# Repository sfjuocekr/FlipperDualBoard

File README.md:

# FlipperDualBoard
A Flipper Zero development board implementing the SPI handles from CFW!

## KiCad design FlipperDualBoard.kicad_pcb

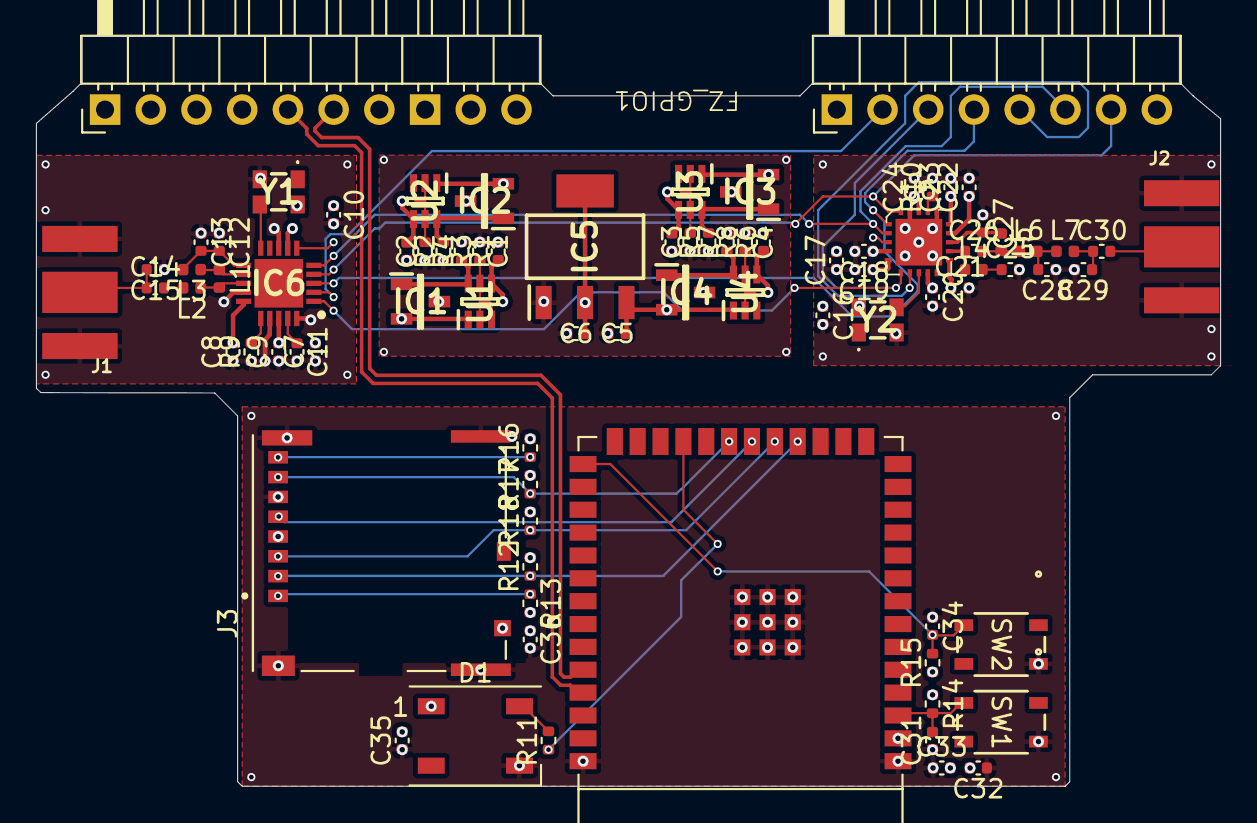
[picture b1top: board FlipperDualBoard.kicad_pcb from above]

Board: 4 copper layers, 65.8 x 41.7 mm, 82 parts (0 on the bottom side), 50 nets.

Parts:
C1, C2, C3, C4, C10, C16, C18, C19, C33, C35, C36: 100nF X7R; C_0402_1005Metric
C5: 10µF NPO; C_0402_1005Metric
C6, C32: 22µF NPO; C_0402_1005Metric
C7, C17: 4.7µF NPO; C_0402_1005Metric
C8, C20, C22: 10nF X7R; C_0402_1005Metric
C9: 1nF X7R; C_0402_1005Metric
C11: 33nF X7R; C_0402_1005Metric
C12: 2.2nF X7R; C_0402_1005Metric
C13: 4.7pF NPO; C_0402_1005Metric
C14: 1.5pF NPO; C_0402_1005Metric
C15: 1pF NPO; C_0402_1005Metric
C21, C23, C24, C25, C30: 220pF NPO; C_0402_1005Metric
C26, C27: 3.9pF NPO; C_0402_1005Metric
C28: 8.2pF NPO; C_0402_1005Metric
C29: 5.6pF NPO; C_0402_1005Metric
C31, C34: 1µF NPO; C_0402_1005Metric
D1: WS2812B; LED_WS2812B_PLCC4_5.0x5.0mm_P3.2mm
FZ_GPIO1: FZ_GPIO
IC1, IC2, IC3, IC4: DMP1045U-7; SOT96P240X120-3N
IC5: AZ1117CH2-3.3TRG1; SOT230P700X180-4N
IC6: nRF24L01P; QFN50P400X400X95-21N-D
J1, J2: Conn_SMA_RF2-143-T-17-50-G; RF_SMA_BoardEdge_RF2-143-T-17-50-G
J3: 503398-1892; MOLEX_503398-1892
L1: 8.2nH; L_0402_1005Metric
L2: 3.9nH; L_0402_1005Metric
L3, L4, L5, L7: 27nH; L_0402_1005Metric
L6: 22nH; L_0402_1005Metric
R1, R2, R3, R4, R5, R6, R7, R8: 100k; R_0402_1005Metric
R9: 22k; R_0402_1005Metric
R10: 56k; R_0402_1005Metric
R11: 220; R_0402_1005Metric
R12, R13, R14, R15, R16, R17, R18: 10k; R_0402_1005Metric
SW1, SW2: SKRPABE010; SW4_SKRPABE010_ALPS
U1, U2, U3, U4: MMDT2907A-7-F; SOT65P210X110-6N
U5: ESP32-S3-WROOM-1
U6: CC1101RGPR; QFN-20-1EP_4x4mm_RevA
Y1: TG2520SMN_16.0000M-MCGNNM3; TG2520SMN160000MMCGNNM3
Y2: TG2520SMN_26.0000M-MCGNNM3; TG2520SMN160000MMCGNNM3

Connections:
/ESP32/BOOT: C34.2, R15.2, SW2.2, U5.27 (GPIO0/BOOT)
/ESP32/CLK: J3.5 (CLK), U5.20 (GPIO12/TOUCH12/ADC2_CH1/FSPICLK/FSPIIO6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)
/ESP32/CMD: J3.3 (CMD), R18.1, U5.19 (GPIO11/TOUCH11/ADC2_CH0/FSPID/FSPIIO5/S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)
/ESP32/DATA0: J3.7 (DAT0), R17.1, U5.21 (GPIO13/TOUCH13/ADC2_CH2/FSPIQ/FSPIIO7/S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)
/ESP32/DATA1: J3.8 (DAT1), R16.1
/ESP32/DATA2: J3.1 (DAT2), R13.1
/ESP32/DATA3: J3.2 (CD/DAT3^2), R12.1, U5.18 (GPIO10/TOUCH10/ADC1_CH9/FSPICS0/FSPIIO4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)
/ESP32/EN: C31.2, R14.2, SW1.2, U5.3 (EN)
/ESP32/U+: FZ_GPIO1.14 (PB7), U5.37 (U0TXD/GPIO43/CLK_OUT1)
/ESP32/U-: FZ_GPIO1.13 (PB6), U5.36 (U0RXD/GPIO44/CLK_OUT2)
/Power Supply/+3v3 IN: C2.1, FZ_GPIO1.9 (3.3v), IC2.3 (D), U2.4 (E2)
/Power Supply/+3v3 LDO: C1.1, C6.1, IC1.3 (D), IC5.2 (ADJ/GND_1), IC5.4 (ADJ/GND_2), U1.4 (E2)
/Power Supply/+3v3 OUT: C7.2, C8.2, C9.2, C10.1, C16.1, C17.2, C18.1, C19.1, C20.1, C21.1, C22.1, C23.1, C24.1, C32.2, C33.2, C35.2, C36.1, D1.1 (VDD), IC1.2 (S), IC2.2 (S), IC6.7 (VDD_1), IC6.15 (VDD_2), IC6.18 (VDD_3), J3.4 (VDD), R12.2, R13.2, R14.1, R15.1, R16.2, R17.2, R18.2, U1.1 (E1), U2.1 (E1), U5.2 (3V3), U6.4 (DVDD), U6.5 (DCOUPL), U6.9 (AVDD), U6.11 (AVDD), U6.14 (AVDD), U6.15 (AVDD), U6.18 (DGUARD), Y1.4 (VCC), Y2.4 (VCC)
/Power Supply/+5v IN: C3.1, FZ_GPIO1.1 (5v), IC3.3 (D), U3.4 (E2)
/Power Supply/+5v OUT: C5.1, IC3.2 (S), IC4.2 (S), IC5.3 (OUTPUT), U3.1 (E1), U4.1 (E1)
/Power Supply/+5v USB: C4.1, IC4.3 (D), U4.4 (E2)
/Power Supply/S0: IC2.1 (G), R4.1, U2.6 (C1)
/Power Supply/S1: IC3.1 (G), R7.1, U3.6 (C1)
/Power Supply/S2: IC1.1 (G), R3.1, U1.6 (C1)
/Power Supply/S3: IC4.1 (G), R8.1, U4.6 (C1)
/SPI Modules/CC1101/RF_N: C27.2, L5.1, U6.13 (RF_N)
/SPI Modules/CC1101/RF_P: C26.1, L4.1, U6.12 (RF_P)
/SPI Modules/CE: FZ_GPIO1.6 (PB2), IC6.1 (CE), U6.6 (GDO0)
/SPI Modules/CS0: FZ_GPIO1.4 (PA4), U6.7 (CSn)
/SPI Modules/CS1: FZ_GPIO1.7 (PC3), IC6.2 (CSN)
/SPI Modules/MISO: FZ_GPIO1.3 (PA6), IC6.5 (MISO), U6.2 (SO(GDO1))
/SPI Modules/MOSI: FZ_GPIO1.2 (PA7), IC6.4 (MOSI), U6.20 (SI)
/SPI Modules/SCK: FZ_GPIO1.5 (PB3), IC6.3 (SCK), U6.1 (SCLK)
GND: C1.2, C2.2, C3.2, C4.2, C5.2, C6.2, C7.1, C8.1, C9.1, C10.2, C11.2, C12.1, C13.1, C15.1, C16.2, C17.1, C18.2, C19.2, C20.2, C21.2, C22.2, C23.2, C24.2, C25.2, C27.1, C28.1, C29.2, C31.1, C32.1, C33.1, C34.1, C35.1, C36.2, D1.3 (VSS), FZ_GPIO1.8 (GND), FZ_GPIO1.11 (GND), FZ_GPIO1.18 (GND), IC5.1 (INPUT), IC6.8 (VSS_1), IC6.14 (VSS_2), IC6.17 (VSS_3), IC6.20 (VSS_4), J1.2, J2.2, J3.6 (VSS), J3.9 (VSS__1), J3.P1 (SHIELD), J3.P2 (SHIELD__1), J3.P3 (SHIELD__2), J3.P4 (SHIELD__3), R1.2, R2.2, R3.2, R4.2, R5.2, R6.2, R7.2, R8.2, R9.1, R10.2, SW1.3, SW2.3, U5.1 (GND), U5.40 (GND), U5.41 (GND), U6.16 (GND), U6.19 (GND), U6.21 (EP_GND), Y1.2 (GND), Y2.2 (GND)
unnamed: C14.1, C15.2, J1.1
unnamed: C14.2, L2.2
unnamed: C25.1, L4.2
unnamed: C26.2, L5.2, L6.1
unnamed: C28.2, L6.2, L7.1
unnamed: C29.1, C30.1, L7.2
unnamed: C30.2, J2.1
unnamed: D1.4 (DIN), R11.2
unnamed: IC6.12 (ANT1), L1.1, L3.1
unnamed: IC6.13 (ANT2), L1.2, L2.1
unnamed: C11.1, IC6.19 (DVDD)
unnamed: IC6.16 (IREF), R9.2
unnamed: C12.2, C13.2, IC6.11 (VDD_PA), L3.2
unnamed: IC6.10 (XC1), Y1.3 (OUT)
unnamed: R1.1, U1.2 (B1), U1.3 (C2), U1.5 (B2)
unnamed: R2.1, U2.2 (B1), U2.3 (C2), U2.5 (B2)
unnamed: R5.1, U3.2 (B1), U3.3 (C2), U3.5 (B2)
unnamed: R6.1, U4.2 (B1), U4.3 (C2), U4.5 (B2)
unnamed: R11.1, U5.23 (GPIO21)
unnamed: R10.1, U6.17 (RBIAS)
unnamed: U6.8 (XOSC_Q1), Y2.3 (OUT)

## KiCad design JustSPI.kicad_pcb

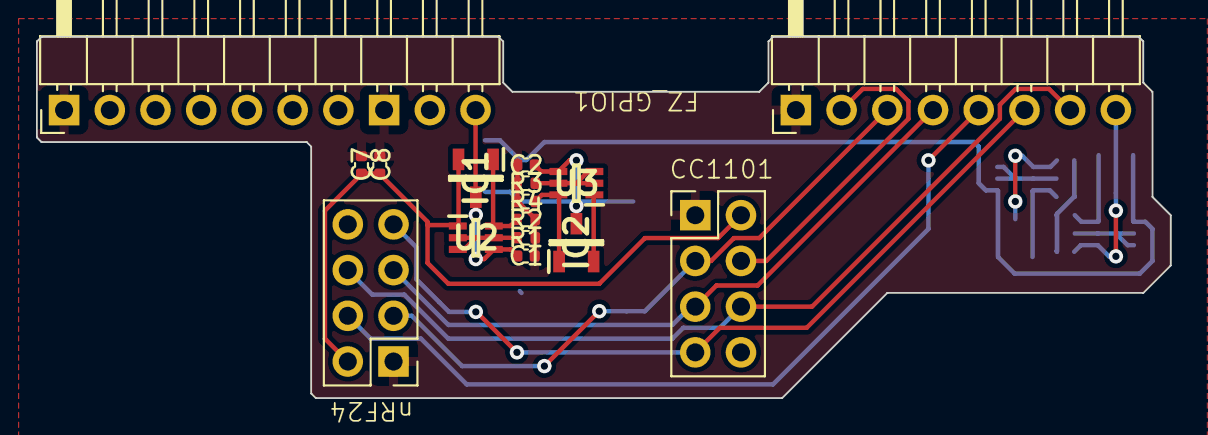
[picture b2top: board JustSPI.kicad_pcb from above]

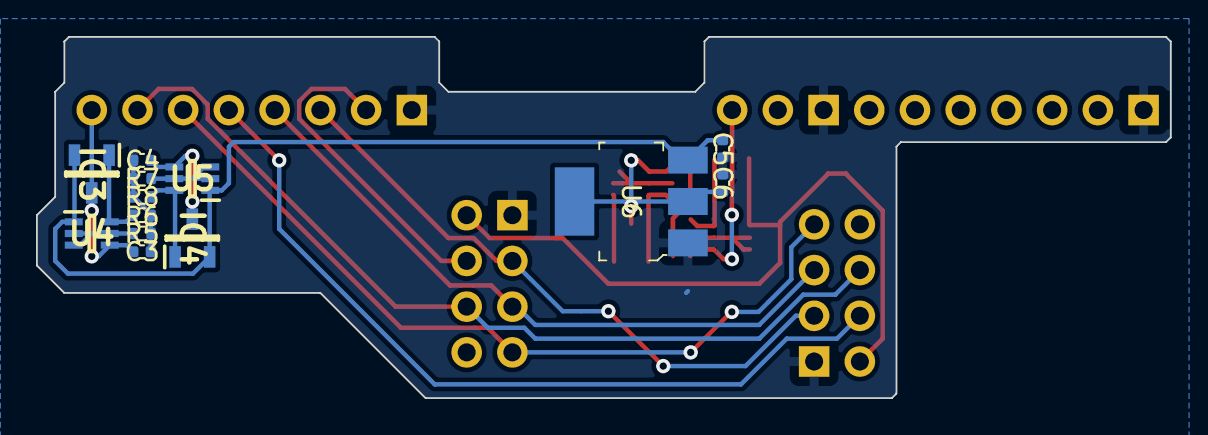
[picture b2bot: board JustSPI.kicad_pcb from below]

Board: 2 copper layers, 63.0 x 20.1 mm, 28 parts (13 on the bottom side), 22 nets.

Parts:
C1, C2, C3, C4, C8: 100nF; C_0402_1005Metric
C5: 10uF; C_0402_1005Metric
C6, C7: 22uF; C_0402_1005Metric
CC1101: CC1101
FZ_GPIO1: FZ_GPIO
IC1, IC2, IC3, IC4: DMP1045U-7; SOT96P240X120-3N
R1, R2, R3, R4, R5, R6, R7, R8: 100k; R_0402_1005Metric
U2, U3, U4, U5: MMDT2907A-7-F; SOT65P210X110-6N
U6: AZ1117CH-3_3TRG1; SOT-223
nRF24: nRF24

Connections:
/+3v3: C7.1, C8.1, CC1101.2 (Vcc), IC1.2 (S), U2.1 (E1), nRF24.2 (Vcc)
/+5v: C5.1, IC3.2 (S), IC4.2 (S), U4.1 (E1), U5.1 (E1), U6.3 (IN)
/Power Supply/+3v3 IN: C1.1, FZ_GPIO1.9 (3.3v), IC1.3 (D), U2.4 (E2)
/Power Supply/+3v3 LDO: C2.1, C6.1, IC2.3 (D), U3.4 (E2), U6.2 (OUT), U6.4 (VOUT)
/Power Supply/+5v IN: C3.1, FZ_GPIO1.1 (5v), IC3.3 (D), U4.4 (E2)
/Power Supply/+5v USB: C4.1, IC4.3 (D), U5.4 (E2)
/SPI Modules/CE: CC1101.3 (CE), FZ_GPIO1.6 (PB2), nRF24.3 (CE)
/SPI Modules/CS0: FZ_GPIO1.4 (PA4), nRF24.4 (CS)
/SPI Modules/CS1: CC1101.4 (CS), FZ_GPIO1.7 (PC3)
/SPI Modules/MISO: CC1101.7 (MISO), FZ_GPIO1.3 (PA6), nRF24.7 (MISO)
/SPI Modules/MOSI: CC1101.6 (MOSI), FZ_GPIO1.2 (PA7), nRF24.6 (MOSI)
/SPI Modules/SCK: CC1101.5 (SCK), FZ_GPIO1.5 (PB3), nRF24.5 (SCK)
GND: C1.2, C2.2, C3.2, C4.2, C5.2, C6.2, C7.2, C8.2, CC1101.1 (GND), FZ_GPIO1.8 (GND), FZ_GPIO1.11 (GND), FZ_GPIO1.18 (GND), R1.2, R2.2, R3.2, R4.2, R5.2, R6.2, R7.2, R8.2, U6.1 (ADJ/GND), nRF24.1 (GND)
unnamed: IC1.1 (G), R2.1, U2.6 (C1)
unnamed: IC2.1 (G), R4.1, U3.6 (C1)
unnamed: IC2.2 (S), U3.1 (E1)
unnamed: IC3.1 (G), R6.1, U4.6 (C1)
unnamed: IC4.1 (G), R8.1, U5.6 (C1)
unnamed: R1.1, U2.2 (B1), U2.3 (C2), U2.5 (B2)
unnamed: R3.1, U3.2 (B1), U3.3 (C2), U3.5 (B2)
unnamed: R5.1, U4.2 (B1), U4.3 (C2), U4.5 (B2)
unnamed: R7.1, U5.2 (B1), U5.3 (C2), U5.5 (B2)

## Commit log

2024-07-14 Initial upload
    This board implements the extra SPI handles exposed by CFW for the Flipper Zero, I've implemented an nRF24, CC1101 and ESP32... the implementation might be completely wrong as I never tested it!
    I had made this board in KiCAD to produce later, but I never got to it so if anyone wants to be the guinea pig here you go!
    Leave me a pile of money if it helped you out <3

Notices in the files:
parts and their libraries:
License: Apache-2.0
